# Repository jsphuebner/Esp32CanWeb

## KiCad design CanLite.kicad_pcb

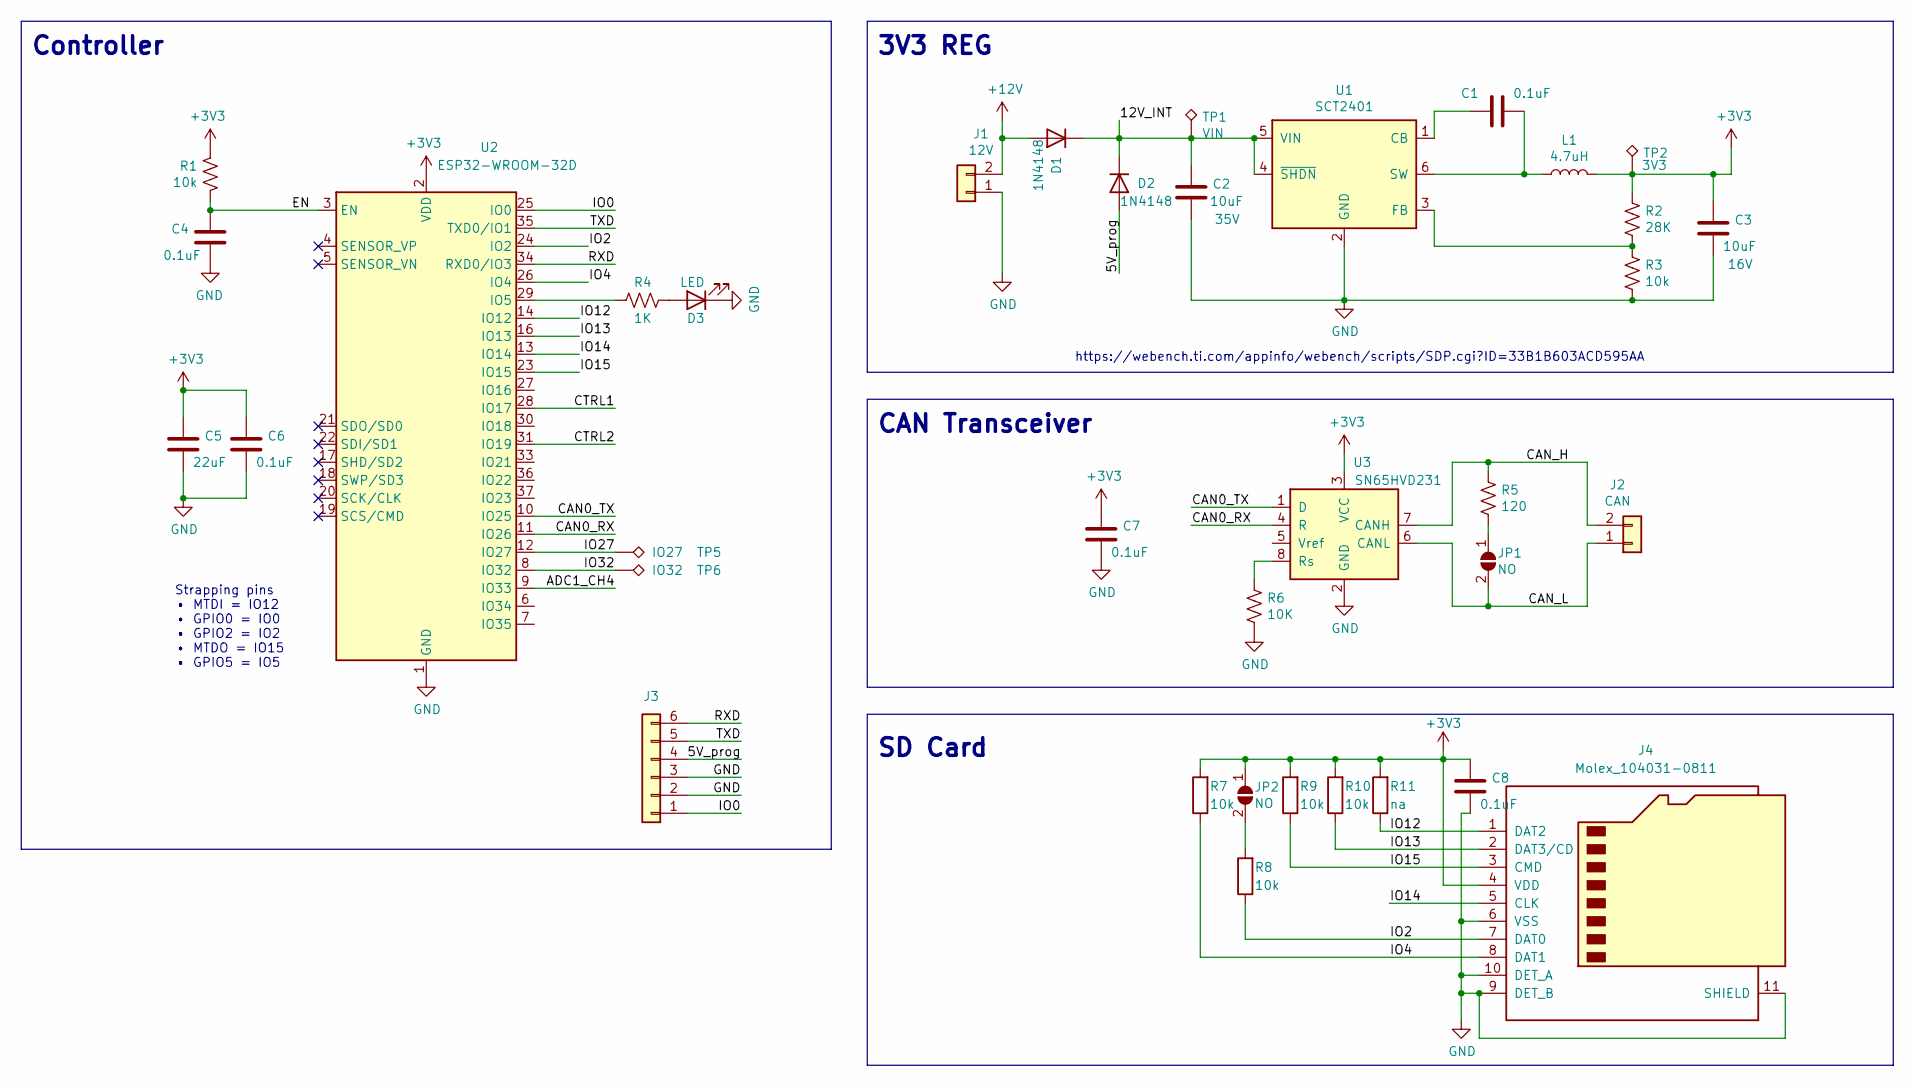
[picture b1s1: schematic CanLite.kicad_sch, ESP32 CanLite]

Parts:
C1, C4, C6, C7, C8: 0.1uF; C_0603_1608Metric; LCSC C14663
C2: 10uF; C_0805_2012Metric; Voltage 35V; LCSC C15850
C3: 10uF; C_0805_2012Metric; Voltage 16V; LCSC C15850
C5: 22uF; C_0805_2012Metric; LCSC C45783
D1, D2: 1N4148; D_SOD-323; LCSC C2128
D3: LED; LED_0603_1608Metric; LCSC C84256
J1: 12V; TerminalBlock_RND_205-00232_1x02_P5.08mm_Horizontal
J2: CAN; TerminalBlock_RND_205-00232_1x02_P5.08mm_Horizontal
J3: PinHeader_1x06_P2.54mm_Vertical
J4: Molex_104031-0811; microSD_HC_Molex_104031-0811; Part 104031-0811; LCSC C330255
JP1, JP2: NO; SolderJumper-2_P1.3mm_Open_TrianglePad1.0x1.5mm
L1: 4.7uH; L_1210_3225Metric; LCSC C90319
R1, R3, R7, R8, R9, R10: 10k; R_0603_1608Metric; LCSC C25804
R2: 28K; R_0603_1608Metric; LCSC C22984
R4: 1K; R_0603_1608Metric; LCSC C21190
R5: 120; R_0603_1608Metric; LCSC C22787
R6: 10K; R_0603_1608Metric
R11: na; R_0603_1608Metric
TP1: VIN; TestPoint_Pad_D1.0mm
TP2: 3V3; TestPoint_Pad_D1.0mm
TP5: IO27; TestPoint_Pad_D1.0mm
TP6: IO32; TestPoint_Pad_D1.0mm
U1: SCT2401; SOT-23-6; LCSC C2830166
U2: ESP32-WROOM-32D; ESP32-WROOM-32; LCSC C82899
U3: SN65HVD231; SOIC-8_3.9x4.9mm_P1.27mm; LCSC C12084

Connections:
+3V3: C3.1, C5.1, C6.1, C7.1, C8.1, J4.4 (VDD), JP2.1 (A), L1.2, R1.1, R2.1, R7.2, R9.2, R10.2, R11.2, TP2.1 (1_1), U2.2 (VDD), U3.3 (VCC)
+12V: D1.2 (A), J1.2
/5V_prog: D2.2 (A), J3.4
/12V_INT: C2.1, D1.1 (K), D2.1 (K), TP1.1 (1_1), U1.4 (~SHDN), U1.5 (VIN)
/ADC1_CH4: U2.9 (IO33)
/CAN0_RX: U2.11 (IO26), U3.4 (R)
/CAN0_TX: U2.10 (IO25), U3.1 (D)
/CAN_H: J2.2, R5.1, U3.7 (CANH)
/CAN_L: J2.1, JP1.2 (B), U3.6 (CANL)
/CTRL1: U2.28 (IO17)
/CTRL2: U2.31 (IO19)
/EN: C4.1, R1.2, U2.3 (EN)
/IO0: J3.1, U2.25 (IO0)
/IO2: J4.7 (DAT0), R8.1, U2.24 (IO2)
/IO4: J4.8 (DAT1), R7.1, U2.26 (IO4)
/IO12: J4.1 (DAT2), R11.1, U2.14 (IO12)
/IO13: J4.2 (DAT3/CD), R10.1, U2.16 (IO13)
/IO14: J4.5 (CLK), U2.13 (IO14)
/IO15: J4.3 (CMD), R9.1, U2.23 (IO15)
/IO27: TP5.1 (1_1), U2.12 (IO27)
/IO32: TP6.1 (1_1), U2.8 (IO32)
/RXD: J3.6, U2.34 (RXD0/IO3)
/TXD: J3.5, U2.35 (TXD0/IO1)
GND: C2.2, C3.2, C4.2, C5.2, C6.2, C7.2, C8.2, D3.1 (K), J1.1, J3.2, J3.3, J4.6 (VSS), J4.9 (DET_B), J4.10 (DET_A), J4.11 (SHIELD), R3.2, R6.2, U1.2 (GND), U2.1 (GND), U2.15 (GND), U2.38 (GND), U2.39 (GND), U3.2 (GND)
unnamed: D3.2 (A), R4.1
unnamed: JP1.1 (A), R5.2
unnamed: JP2.2 (B), R8.2
unnamed: C1.1, U1.1 (CB)
unnamed: R2.2, R3.1, U1.3 (FB)
unnamed: C1.2, L1.1, U1.6 (SW)
unnamed: R4.2, U2.29 (IO5)
unnamed: R6.1, U3.8 (Rs)

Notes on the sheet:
SD Card
3V3 REG
Controller
CAN Transceiver
Strapping pins • MTDI = IO12 • GPIO0 = IO0 • GPIO2 = IO2 • MTDO = IO15 • GPIO5 = IO5
https://webench.ti.com/appinfo/webench/scripts/SDP.cgi?ID=33B1B603ACD595AA

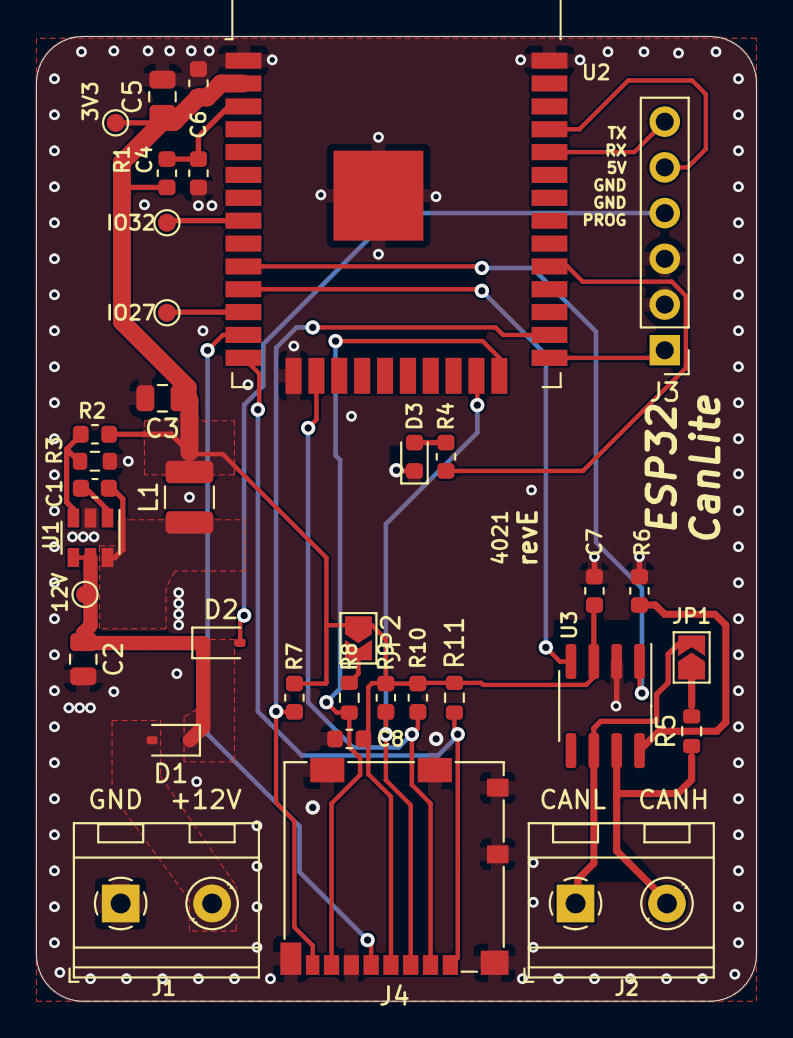
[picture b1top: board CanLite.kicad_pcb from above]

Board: 2 copper layers, 40.0 x 53.6 mm, 36 parts (0 on the bottom side), 29 nets.

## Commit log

2026-06-16 Kicad 10 + RevE: protect 5V_prog
